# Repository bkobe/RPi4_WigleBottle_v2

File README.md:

# RPi4_WigleBottle_v2
A Raspberry Pi 4 Wigle Bottle USB 2 Breakout Board
B. Kobe - June, 2022

DISCLAIMER: I do not accept responsibility for use of the board, other than intended as a breakout board to increase spacing of hardware ports of a stock Raspberry Pi 4 single board computer.  Use at your own risk. With that said, Let's get into the build...

This board increases the spacing of the traditional Raspberry Pi 4 USB 2 ports (does not support USB 3 on the ports that do -- for reasons later on). Primary design of the board is for an https://wigle.net collector using USB dongles as data sources (WiFi, Bluetooth, GPS) in a portable form factor.  Boards are shared on OSH Park and can be ordered here in sets of three: https://oshpark.com/shared_projects/4ibeuOBA.

The schematic PDF has the bill of materials (BOM) in it, which lists the parts and digikey reference numbers for easy ordering.  There are 4x resistors and LEDs (0805 or 1206 surface mount style) for indicating each USB's Vbus power, 4x filtering capacitors for each Vbus, and 4x USB plugs and sockets for power and data.  The resistors and LEDs can be omitted if desired for even lower power operation.  

For assembling the board, solder on all surface mount components first.  The LEDs (middle component for each group) are directional, and the cathode is oriented to the middle of the board.  For the 0805 LEDs in the picture below, this is denoted by a green dot/mark within the clear case. All LEDs "point" inward away from the respective USB connector.  

Once the surface mount components are installed, take the USB plugs, and bend in the tabs and straighten the pins.  I was not able to find suitable vertical-style plugs (for a decent cost), and stock horizontal board mounts are easily adapted.  

Put all the USB plugs into the host Raspberry Pi 4, so we get all the pins aligned for the board. Place the board onto the Pi, aligning all the pins (hint, start at one end, angle the board, and insert each pin as you decrease the angle to being flat and all pins inserted into the board. The proper oritentation is silkscreen side up, and the notch aligns with the ethernet socket.  CAUTION: Previous versions of the Raspberry Pi (2/3) have the USB and ethernet sockets flipped, this board will not work to adapt to the previous layout.  

After soldering in all the pins for 4x USB plugs (and since we bent in the tabs that would normally strengthen the USB port to the board), place some solder on the side pads of each port, creating a fillet of solder to bridge the side of USB plug to the board. 

Remove the board now from the Pi, and lastly, solder in all the USB sockets top-side (silkscreen side) of the board.  Align the tabs and pins, and push into the board. 

To finish up the board after fluxing and solder, clean the board up with some rubbing/isopropyl alcohol.  It is now ready to use with any USB 2 dongle!  

Some design notes for in-depth interest:
* USB D+/D- lines in Kicad have a skew (difference) from almost nothing (completely equal), up to a few percent.  The USB-2 Specification allows up to a 10% skew in the data lines for reliable communication.  D+/D- lines on the board have a 90 ohm impedance to the ground plane (top-side). 
* Although the Pi 3 can support USB-3 on two ports, This becomes problematic for electromagnetic interference, especially on a simple 2 layer board.  Rather than trying to build in 2x USB-3 ports and increasing cost/design of a board that supports it, USB-2 was used on the ports. This keeps potential interference to less than 480 MHz (480 Mbps USB clock), rather than potential interference up into the 1-2 GHz range (USB-3 has a strong spur in the 1500 MHz range with some poorly shielded cables, interfering with close proximity GPS antennas/receivers).  
* Board was designed in KiCad 6.  All associated files are located in the /kicad directory, along with the gerbers for your own fabrication.

Enjoy, and happy wardriving!

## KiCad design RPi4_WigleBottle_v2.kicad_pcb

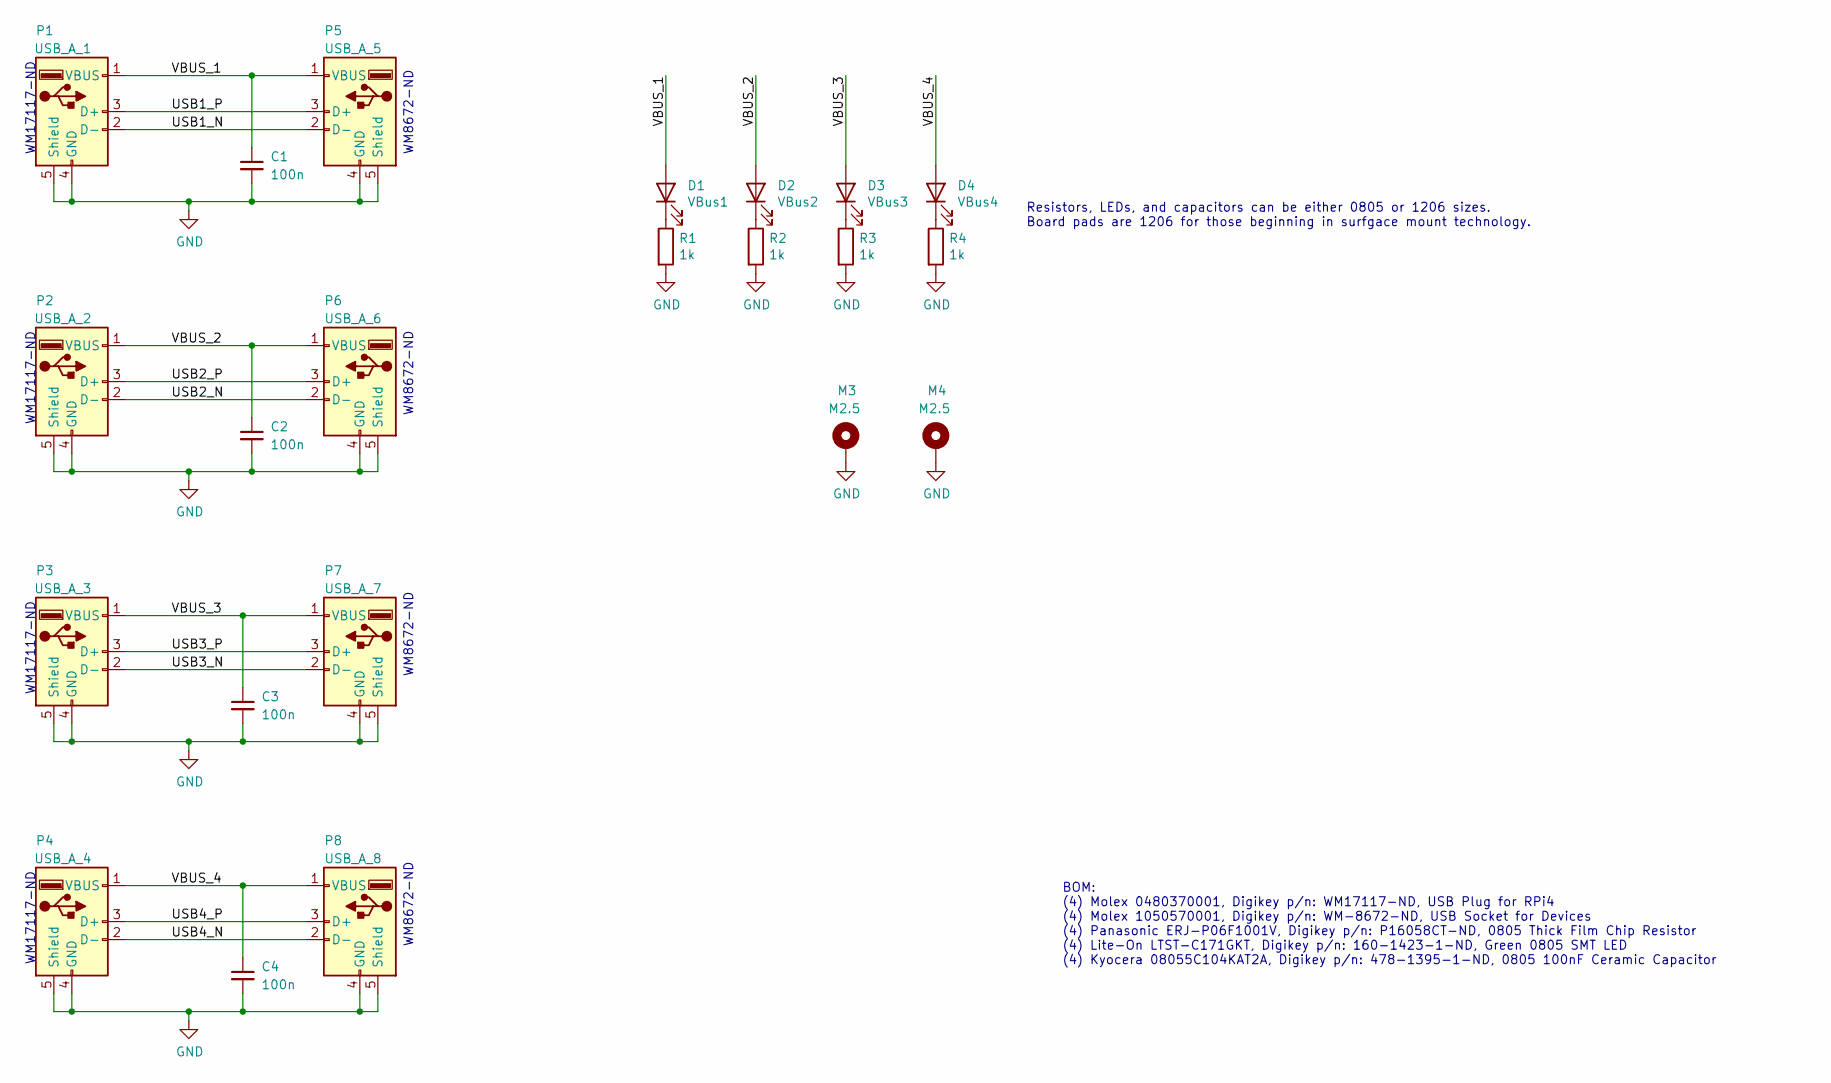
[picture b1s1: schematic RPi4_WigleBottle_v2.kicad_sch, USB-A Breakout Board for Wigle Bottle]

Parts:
C1, C2, C3, C4: 100n; C_1206_3216Metric
D1: VBus1; LED_1206_3216Metric
D2: VBus2; LED_1206_3216Metric
D3: VBus3; LED_1206_3216Metric
D4: VBus4; LED_1206_3216Metric
M3, M4: M2.5; MountingHole_2.7mm_Pad_Via
P1: USB_A_1; USB_A_Molex_0480370001_Vertical
P2: USB_A_2; USB_A_Molex_0480370001_Vertical
P3: USB_A_3; USB_A_Molex_0480370001_Vertical
P4: USB_A_4; USB_A_Molex_0480370001_Vertical
P5: USB_A_5; USB_A_Molex_105057_Vertical
P6: USB_A_6; USB_A_Molex_105057_Vertical
P7: USB_A_7; USB_A_Molex_105057_Vertical
P8: USB_A_8; USB_A_Molex_105057_Vertical
R1, R2, R3, R4: 1k; R_1206_3216Metric

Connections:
/USB1_N: P1.2 (D-), P5.2 (D-)
/USB1_P: P1.3 (D+), P5.3 (D+)
/USB2_N: P2.2 (D-), P6.2 (D-)
/USB2_P: P2.3 (D+), P6.3 (D+)
/USB3_N: P3.2 (D-), P7.2 (D-)
/USB3_P: P3.3 (D+), P7.3 (D+)
/USB4_N: P4.2 (D-), P8.2 (D-)
/USB4_P: P4.3 (D+), P8.3 (D+)
/VBUS_1: C1.1, D1.2 (A), P1.1 (VBUS), P5.1 (VBUS)
/VBUS_2: C2.1, D2.2 (A), P2.1 (VBUS), P6.1 (VBUS)
/VBUS_3: C3.1, D3.2 (A), P3.1 (VBUS), P7.1 (VBUS)
/VBUS_4: C4.1, D4.2 (A), P4.1 (VBUS), P8.1 (VBUS)
GND: C1.2, C2.2, C3.2, C4.2, M3.1, M4.1, P1.4 (GND), P1.5 (Shield), P2.4 (GND), P2.5 (Shield), P3.4 (GND), P3.5 (Shield), P4.4 (GND), P4.5 (Shield), P5.4 (GND), P5.5 (Shield), P6.4 (GND), P6.5 (Shield), P7.4 (GND), P7.5 (Shield), P8.4 (GND), P8.5 (Shield), R1.2, R2.2, R3.2, R4.2
unnamed: D1.1 (K), R1.1
unnamed: D2.1 (K), R2.1
unnamed: D3.1 (K), R3.1
unnamed: D4.1 (K), R4.1

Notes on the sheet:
WM17117-ND
BOM: (4) Molex 0480370001, Digikey p/n: WM17117-ND, USB Plug for RPi4 (4) Molex 1050570001, Digikey p/n: WM-8672-ND, USB Socket for Devices (4) Panasonic ERJ-P06F1001V, Digikey p/n: P16058CT-ND, 0805 Thick Film Chip Resistor (4) Lite-On LTST-C171GKT, Digikey p/n: 160-1423-1-ND, Green 0805 SMT LED (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
WM8672-ND
Resistors, LEDs, and capacitors can be either 0805 or 1206 sizes. Board pads are 1206 for those beginning in surfgace mount technology.

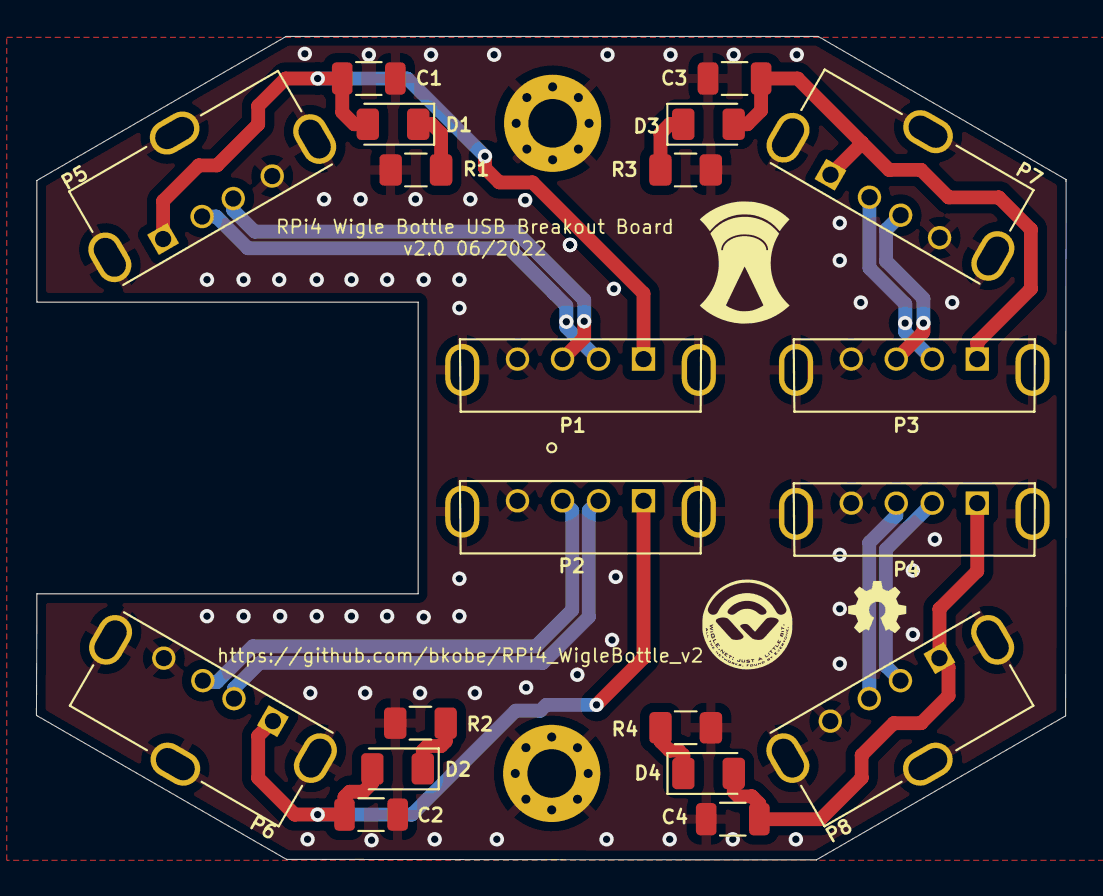
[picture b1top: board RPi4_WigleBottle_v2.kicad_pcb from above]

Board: 2 copper layers, 57.2 x 45.7 mm, 22 parts (0 on the bottom side), 17 nets.

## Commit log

2022-07-16 Update README.md
    initial commit of the README.md for tutorial.
2022-07-18 Added in KiCAD files
